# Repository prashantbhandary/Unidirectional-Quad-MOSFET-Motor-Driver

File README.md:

# Unidirectional Quad-MOSFET Motor Driver

This repository contains the KiCad project files for a unidirectional quad-MOSFET motor driver PCB. The design provides four MOSFETs arranged to drive a motor in a single direction (useful for simple brushed DC motor control, high-side or low-side switching depending on the schematic), with supporting passive components and connectors.

## What’s included

- `Unidirectional Quad-MOSFET Motor Driver.kicad_pro` — KiCad project file
- `Unidirectional Quad-MOSFET Motor Driver.kicad_sch` — KiCad schematic sheet
- `Unidirectional Quad-MOSFET Motor Driver.kicad_pcb` — KiCad PCB layout
- `Unidirectional Quad-MOSFET Motor Driver.kicad_prl` — PCB print/plot settings
- `fp-info-cache/` — footprint cache used by KiCad
- `Unidirectional Quad-MOSFET Motor Driver-backups/` — automatic backups exported by KiCad

> Note: Filenames are case-sensitive on some platforms. Keep the project files together in the same folder.

## Project images

Below are a couple of images included in this folder. They are referenced with relative paths so they render on GitHub and locally.

3D view of the PCB:

Main schematic preview:

## Bill of Materials (BOM)

The interactive BOM (ibom) is available in the `bom/` folder. View it locally or on GitHub by clicking link below:

<div>
	<a href="bom/ibom.html" style="color: #c0392b; font-weight: 600;">Open interactive BOM (ibom.html)</a>
</div>

## Recommended KiCad version

This project was created with KiCad 6.x — KiCad 6 or later is recommended to avoid compatibility issues. If you open the project in an older KiCad version, make a backup first.

## How to open the project

1. Install KiCad (6.x or later): https://kicad.org
2. Open KiCad and select `File > Open Project...` and choose `Unidirectional Quad-MOSFET Motor Driver.kicad_pro` in this folder.
3. Inspect the schematic first (`.kicad_sch`), then open the PCB (`.kicad_pcb`).

## Contributing

If you make improvements (BOM, layout changes, footprint fixes, or add gerbers), please contribute back by creating a PR or adding files to this repo.

## Contact

Add your name and contact details here if you wish to attribute authorship or allow maintainers to contact you regarding the design.

Author: Prashant Bhandari

Email: info@bhandari-prashant.com.np

Phone: +977 9867756915

Location: Pokhara, Nepal

Website: https://bhandari-prashant.com.np/

Social:
- LinkedIn: https://www.linkedin.com/in/prashantbdri
- GitHub: https://github.com/prashantbhandary
- Twitter: https://twitter.com/prasahant_usr
- Instagram: https://www.instagram.com/_prashant.08/

Short bio: Electronics Engineering student (B.E.) specializing in Robotics, PCB design, and embedded systems. See https://bhandari-prashant.com.np/ for full profile and projects.

---

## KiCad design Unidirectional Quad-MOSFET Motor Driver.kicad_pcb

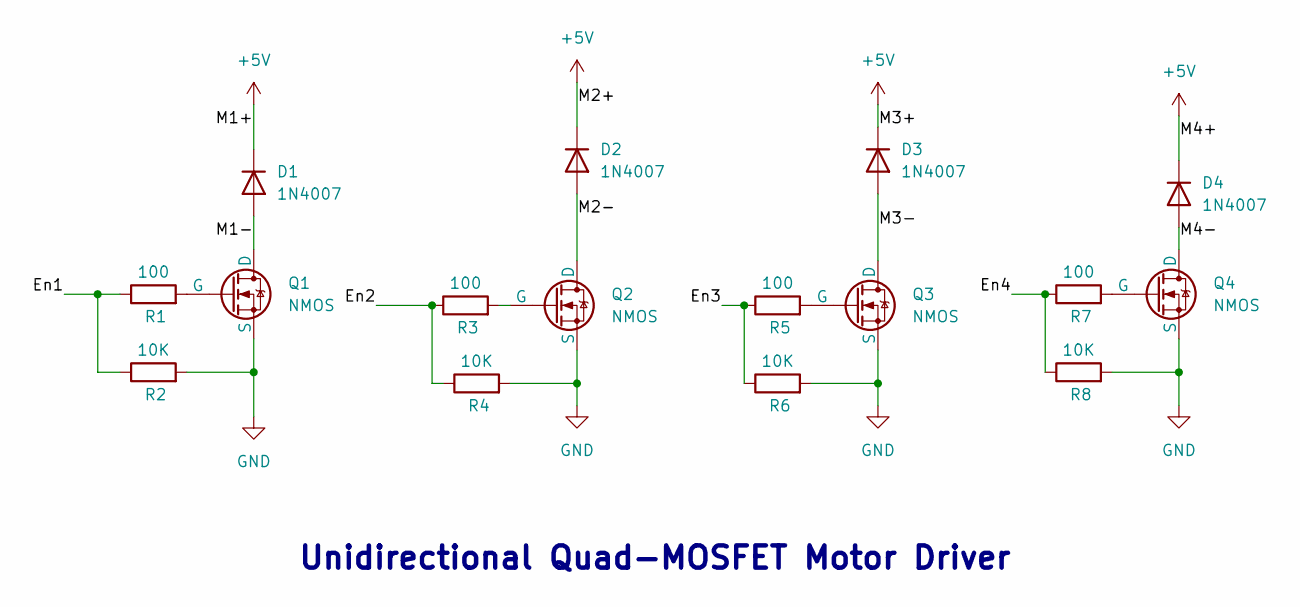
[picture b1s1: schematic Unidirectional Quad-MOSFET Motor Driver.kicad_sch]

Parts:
D1, D2, D3, D4: 1N4007; D_SOD-123
Q1, Q2, Q3, Q4: NMOS; SOT-23
R1, R3, R5, R7: 100; R_0805_2012Metric
R2, R4, R6, R8: 10K; R_0805_2012Metric

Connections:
+5V: D1.1 (K), D2.1 (K), D3.1 (K), D4.1 (K)
/En1: R1.1, R2.1
/En2: R3.1, R4.1
/En3: R5.1, R6.1
/En4: R7.1, R8.1
/M1-: D1.2 (A), Q1.1 (D)
/M2-: D2.2 (A), Q2.1 (D)
/M3-: D3.2 (A), Q3.1 (D)
/M4-: D4.2 (A), Q4.1 (D)
GND: Q1.3 (S), Q2.3 (S), Q3.3 (S), Q4.3 (S), R2.2, R4.2, R6.2, R8.2
unnamed: Q1.2 (G), R1.2
unnamed: Q2.2 (G), R3.2
unnamed: Q3.2 (G), R5.2
unnamed: Q4.2 (G), R7.2

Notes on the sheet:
Unidirectional Quad-MOSFET Motor Driver

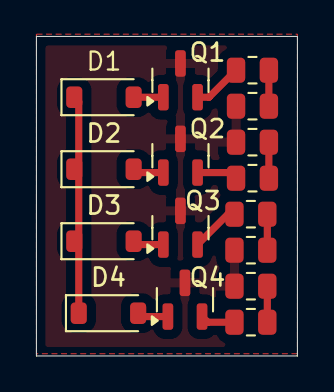
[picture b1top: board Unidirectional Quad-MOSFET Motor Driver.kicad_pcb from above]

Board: 2 copper layers, 14.5 x 17.8 mm, 16 parts (0 on the bottom side), 14 nets.

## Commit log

2025-10-05 Unidirectional Quad-MOSFET Motor Driver
2025-10-05 Fix .gitattributes patterns for Linguist (use literal paths)
2025-10-05 Trigger GitHub Linguist reanalysis
2025-10-05 Unidirectional Quad-MOSFET Motor Driver rmv attr
